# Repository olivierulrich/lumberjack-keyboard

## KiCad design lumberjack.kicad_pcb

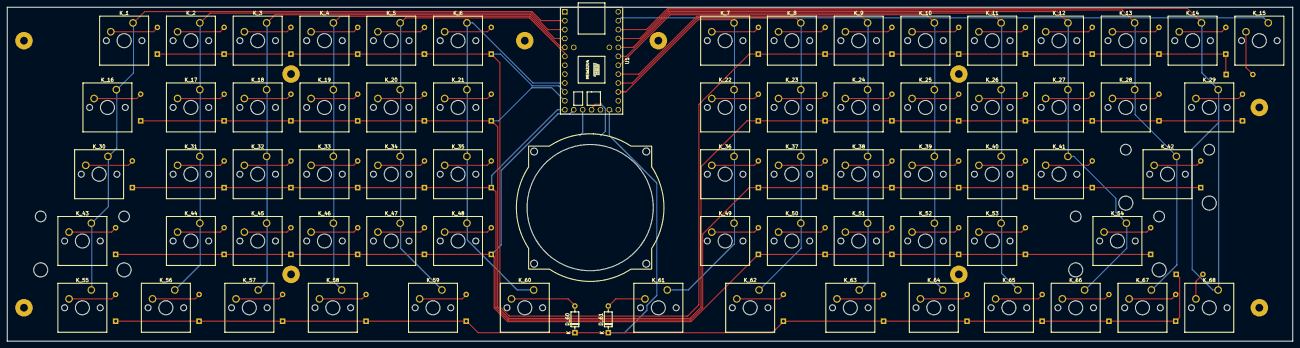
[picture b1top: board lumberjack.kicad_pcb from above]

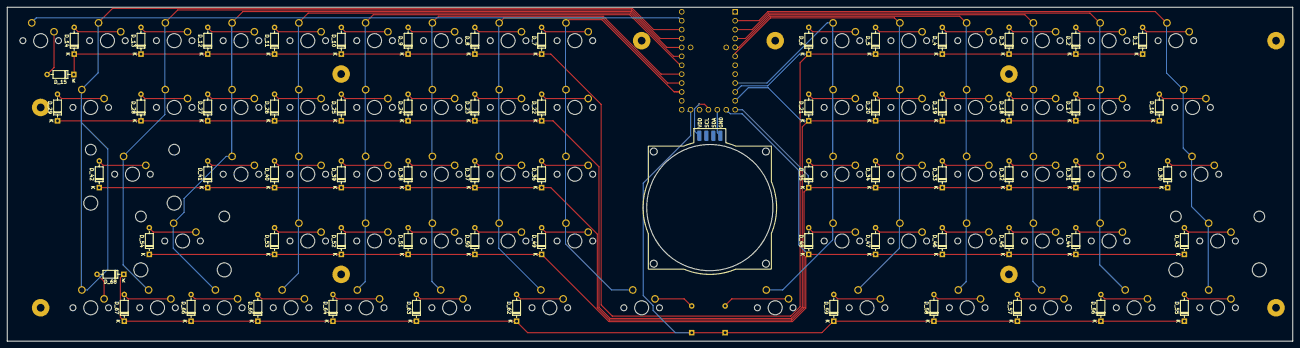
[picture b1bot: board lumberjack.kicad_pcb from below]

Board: 2 copper layers, 366.7 x 95.2 mm, 148 parts (66 on the bottom side), 92 nets.

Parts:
D_1, D_2, D_3, D_4, D_5, D_6, D_7, D_8, D_9, D_10, D_11, D_12, D_13, D_14, D_15, D_16, D_17, D_18, D_19, D_20, D_21, D_22, D_23, D_24, D_25, D_26, D_27, D_28, D_29, D_30, D_31, D_32, D_33, D_34, D_35, D_36, D_37, D_38, D_39, D_40, D_41, D_42, D_43, D_44, D_45, D_46, D_47, D_48, D_49, D_50, D_51, D_52, D_53, D_54, D_55, D_56, D_57, D_58, D_59, D_60, D_61, D_62, D_63, D_64, D_65, D_66, D_67, D_68: 1N4148; D_DO-35_SOD27_P7.62mm_Horizontal
H1, H3, H4, H5, H6, H8, H9, H10, H11, H12: M2; MountingHole_M2
K_1, K_2, K_3, K_4, K_5, K_6, K_7, K_8, K_9, K_10, K_11, K_12, K_13, K_14, K_15, K_17, K_18, K_19, K_20, K_21, K_22, K_23, K_24, K_25, K_26, K_27, K_28, K_31, K_32, K_33, K_34, K_35, K_36, K_37, K_38, K_39, K_40, K_41, K_44, K_45, K_46, K_47, K_48, K_49, K_50, K_51, K_52, K_53, K_60, K_61, K_65, K_66, K_67, K_68: KEYSW; SW_Cherry_MX_1.00u_PCB
K_16, K_29: KEYSW; SW_Cherry_MX_1.50u_PCB
K_30, K_59, K_62: KEYSW; SW_Cherry_MX_1.75u_PCB
K_42, K_43: KEYSW; SW_Cherry_MX_2.25u_PCB
K_54: KEYSW; SW_Cherry_MX_2.75u_PCB
K_55, K_56, K_57, K_58, K_63, K_64: KEYSW; SW_Cherry_MX_1.25u_PCB
U1: Teensy2.0_(C); Teensy2.0
U2: Cirque40mm; cirque_40mm

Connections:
COL0: K_1.1 (COL), K_16.1 (COL), K_30.1 (COL), K_43.1 (COL), K_55.1 (COL), U1.2 (PB0_SS)
COL1: K_2.1 (COL), K_17.1 (COL), K_31.1 (COL), K_44.1 (COL), K_56.1 (COL), U1.3 (PB1_SCLK)
COL2: K_3.1 (COL), K_18.1 (COL), K_32.1 (COL), K_45.1 (COL), K_57.1 (COL), U1.4 (PB2_MOSI)
COL3: K_4.1 (COL), K_19.1 (COL), K_33.1 (COL), K_46.1 (COL), K_58.1 (COL), U1.5 (PB3_MISO)
COL4: K_5.1 (COL), K_20.1 (COL), K_34.1 (COL), K_47.1 (COL), K_59.1 (COL), U1.6 (PB7_OC0A_OC1C_RTS)
COL5: K_6.1 (COL), K_21.1 (COL), K_35.1 (COL), K_48.1 (COL), K_60.1 (COL), U1.9 (PD2_INT2_RXD1)
COL6: K_7.1 (COL), K_22.1 (COL), K_36.1 (COL), K_49.1 (COL), K_61.1 (COL), U1.20 (PB4_ADC11)
COL7: K_8.1 (COL), K_23.1 (COL), K_37.1 (COL), K_50.1 (COL), K_62.1 (COL), U1.21 (PB5_ADC12_OC1A_OB4B)
COL8: K_9.1 (COL), K_24.1 (COL), K_38.1 (COL), K_51.1 (COL), K_63.1 (COL), U1.22 (PB6_ADC13_OC1B_OC4B)
COL9: K_10.1 (COL), K_25.1 (COL), K_39.1 (COL), K_52.1 (COL), K_64.1 (COL), U1.23 (PF7_ADC7)
COL10: K_11.1 (COL), K_26.1 (COL), K_40.1 (COL), K_53.1 (COL), K_65.1 (COL), U1.24 (PF6_ADC6)
COL11: K_12.1 (COL), K_27.1 (COL), K_41.1 (COL), K_54.1 (COL), K_66.1 (COL), U1.25 (PF5_ADC5)
COL12: K_13.1 (COL), K_28.1 (COL), K_42.1 (COL), K_67.1 (COL), U1.26 (PF4_ADC4)
COL13: K_14.1 (COL), K_29.1 (COL), K_68.1 (COL), U1.27 (PF1_ADC1)
COL14: K_15.1 (COL), U1.28 (PF0_ADC0)
unnamed: D_1.2 (A), K_1.2 (ROW)
unnamed: D_2.2 (A), K_2.2 (ROW)
unnamed: D_3.2 (A), K_3.2 (ROW)
unnamed: D_4.2 (A), K_4.2 (ROW)
unnamed: D_5.2 (A), K_5.2 (ROW)
unnamed: D_6.2 (A), K_6.2 (ROW)
unnamed: D_7.2 (A), K_7.2 (ROW)
unnamed: D_8.2 (A), K_8.2 (ROW)
unnamed: D_9.2 (A), K_9.2 (ROW)
unnamed: D_10.2 (A), K_10.2 (ROW)
unnamed: D_11.2 (A), K_11.2 (ROW)
unnamed: D_12.2 (A), K_12.2 (ROW)
unnamed: D_13.2 (A), K_13.2 (ROW)
unnamed: D_14.2 (A), K_14.2 (ROW)
unnamed: D_15.2 (A), K_15.2 (ROW)
unnamed: D_16.2 (A), K_16.2 (ROW)
unnamed: D_17.2 (A), K_17.2 (ROW)
unnamed: D_18.2 (A), K_18.2 (ROW)
unnamed: D_19.2 (A), K_19.2 (ROW)
unnamed: D_20.2 (A), K_20.2 (ROW)
unnamed: D_21.2 (A), K_21.2 (ROW)
unnamed: D_22.2 (A), K_22.2 (ROW)
unnamed: D_23.2 (A), K_23.2 (ROW)
unnamed: D_24.2 (A), K_24.2 (ROW)
unnamed: D_25.2 (A), K_25.2 (ROW)
unnamed: D_26.2 (A), K_26.2 (ROW)
unnamed: D_27.2 (A), K_27.2 (ROW)
unnamed: D_28.2 (A), K_28.2 (ROW)
unnamed: D_29.2 (A), K_29.2 (ROW)
unnamed: D_30.2 (A), K_30.2 (ROW)
unnamed: D_31.2 (A), K_31.2 (ROW)
unnamed: D_32.2 (A), K_32.2 (ROW)
unnamed: D_33.2 (A), K_33.2 (ROW)
unnamed: D_34.2 (A), K_34.2 (ROW)
unnamed: D_35.2 (A), K_35.2 (ROW)
unnamed: D_36.2 (A), K_36.2 (ROW)
unnamed: D_37.2 (A), K_37.2 (ROW)
unnamed: D_38.2 (A), K_38.2 (ROW)
unnamed: D_39.2 (A), K_39.2 (ROW)
unnamed: D_40.2 (A), K_40.2 (ROW)
unnamed: D_41.2 (A), K_41.2 (ROW)
unnamed: D_42.2 (A), K_42.2 (ROW)
unnamed: D_43.2 (A), K_43.2 (ROW)
unnamed: D_44.2 (A), K_44.2 (ROW)
unnamed: D_45.2 (A), K_45.2 (ROW)
unnamed: D_46.2 (A), K_46.2 (ROW)
unnamed: D_47.2 (A), K_47.2 (ROW)
unnamed: D_48.2 (A), K_48.2 (ROW)
unnamed: D_49.2 (A), K_49.2 (ROW)
unnamed: D_50.2 (A), K_50.2 (ROW)
unnamed: D_51.2 (A), K_51.2 (ROW)
unnamed: D_52.2 (A), K_52.2 (ROW)
unnamed: D_53.2 (A), K_53.2 (ROW)
unnamed: D_54.2 (A), K_54.2 (ROW)
unnamed: D_55.2 (A), K_55.2 (ROW)
unnamed: D_56.2 (A), K_56.2 (ROW)
unnamed: D_57.2 (A), K_57.2 (ROW)
unnamed: D_58.2 (A), K_58.2 (ROW)
unnamed: D_59.2 (A), K_59.2 (ROW)
unnamed: D_60.2 (A), K_60.2 (ROW)
unnamed: D_61.2 (A), K_61.2 (ROW)
unnamed: D_62.2 (A), K_62.2 (ROW)
unnamed: D_63.2 (A), K_63.2 (ROW)
unnamed: D_64.2 (A), K_64.2 (ROW)
unnamed: D_65.2 (A), K_65.2 (ROW)
unnamed: D_66.2 (A), K_66.2 (ROW)
unnamed: D_67.2 (A), K_67.2 (ROW)
unnamed: D_68.2 (A), K_68.2 (ROW)
unnamed: U1.7 (PD0_INT0_SCL_OC0B), U2.2 (SCL)
unnamed: U1.8 (PD1_INT1_SDA), U2.3 (SDA)
unnamed: U1.15 (GND), U2.1 (GND)
unnamed: U1.14 (VCC), U2.4 (VDD)
ROW0: D_1.1 (K), D_2.1 (K), D_3.1 (K), D_4.1 (K), D_5.1 (K), D_6.1 (K), D_7.1 (K), D_8.1 (K), D_9.1 (K), D_10.1 (K), D_11.1 (K), D_12.1 (K), D_13.1 (K), D_14.1 (K), D_15.1 (K), U1.10 (PD3_INT3_TXD1)
ROW1: D_16.1 (K), D_17.1 (K), D_18.1 (K), D_19.1 (K), D_20.1 (K), D_21.1 (K), D_22.1 (K), D_23.1 (K), D_24.1 (K), D_25.1 (K), D_26.1 (K), D_27.1 (K), D_28.1 (K), D_29.1 (K), U1.11 (PC6_OC3A_OC4A)
ROW2: D_30.1 (K), D_31.1 (K), D_32.1 (K), D_33.1 (K), D_34.1 (K), D_35.1 (K), D_36.1 (K), D_37.1 (K), D_38.1 (K), D_39.1 (K), D_40.1 (K), D_41.1 (K), D_42.1 (K), U1.12 (PC7_ICP3_OC4A)
ROW3: D_43.1 (K), D_44.1 (K), D_45.1 (K), D_46.1 (K), D_47.1 (K), D_48.1 (K), D_49.1 (K), D_50.1 (K), D_51.1 (K), D_52.1 (K), D_53.1 (K), D_54.1 (K), U1.13 (PD5_XCK1_CTS)
ROW4: D_55.1 (K), D_56.1 (K), D_57.1 (K), D_58.1 (K), D_59.1 (K), D_60.1 (K), D_61.1 (K), D_62.1 (K), D_63.1 (K), D_64.1 (K), D_65.1 (K), D_66.1 (K), D_67.1 (K), D_68.1 (K), U1.17 (PD4_ADC8_ICP1)

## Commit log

2023-05-29 add rows 13-17 to schematic
2023-05-29 truncate last col bc of uneven row layout
2023-05-29 update pcb
2023-05-29 layout new switches and diodes
2023-05-30 new IC and updated col layout
2023-06-05 layout traces
2023-06-05 new layout
2023-06-09 middle part layout and traces
2023-06-09 usb mini and traces
2023-06-10 gerber output
2023-06-23 change dimensions to fit handrest
2023-07-28 replace mcu with teensy
2023-07-28 add kb layout file
2023-08-06 add cirque trackpad
